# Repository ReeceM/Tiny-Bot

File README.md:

Tiny-Bot
========

ATTiny light influenced robot source code and board design files

This is the repository for the Tiny Bot that I designed after being influenced by the design of born 2 craft light bot.

Code
========
The code is written in the Arduino IDE as it was the quickest way to change and flash code when building(to me).
I plan to change it over to to correct C++ in months to come to shrink code size.

Design 
========

The design can be found at http://bariumelectronics.blogspot.com/2014/12/tiny-bot.html

Please feel free to edit and share your ideas :)

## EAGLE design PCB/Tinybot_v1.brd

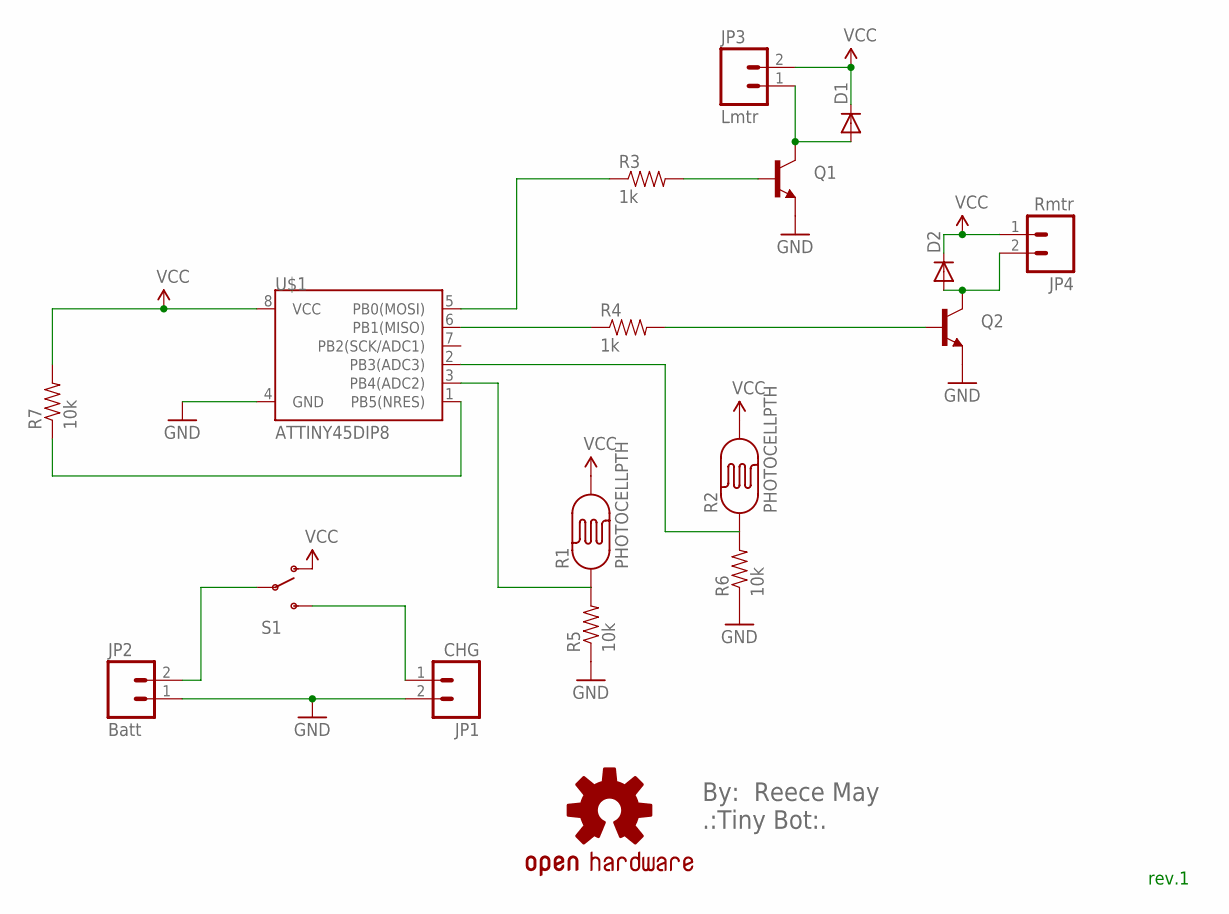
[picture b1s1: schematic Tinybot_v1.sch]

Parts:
D1, D2: DIODESOD; SOD-323
JP1: CHG; 1X02
JP2: Batt; 1X02
JP3: Lmtr; 1X02
JP4: Rmtr; 1X02
Q1, Q2: TRANSISTOR_NPNSOT23; SOT23
R1, R2: PHOTOCELLPTH; PHOTOCELL
R3, R4: 1k; 0805
R5, R6, R7: 10k; 0805
S1: SWITCH-SPST-SMD-A
U$1: ATTINY45DIP8; DIP08
U$2: OSHW-LOGOM; OSHW-LOGO-M

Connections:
GND: JP1.2, JP2.1, Q1.2 (E), Q2.2 (E), R5.1, R6.1, U$1.4 (GND)
unnamed: R3.1, U$1.5 (PB0(MOSI))
unnamed: R4.1, U$1.6 (PB1(MISO))
unnamed: Q1.1 (B), R3.2
unnamed: Q2.1 (B), R4.2
unnamed: D1.2 (A), JP3.1, Q1.3 (C)
unnamed: D2.2 (A), JP4.2, Q2.3 (C)
unnamed: JP2.2, S1.2
unnamed: JP1.1, S1.3 (S)
unnamed: R2.1, R6.2, U$1.2 (PB3(ADC3))
unnamed: R1.1, R5.2, U$1.3 (PB4(ADC2))
unnamed: R7.1, U$1.1 (PB5(NRES))
VCC: D1.1 (C), D2.1 (C), JP3.2, JP4.1, R1.2, R2.2, R7.2, S1.1 (O), U$1.8 (VCC)

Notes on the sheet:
By: Reece May .:Tiny Bot:.
rev.1

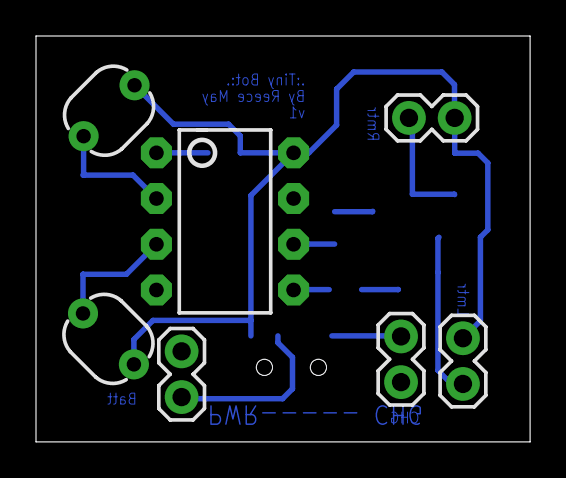
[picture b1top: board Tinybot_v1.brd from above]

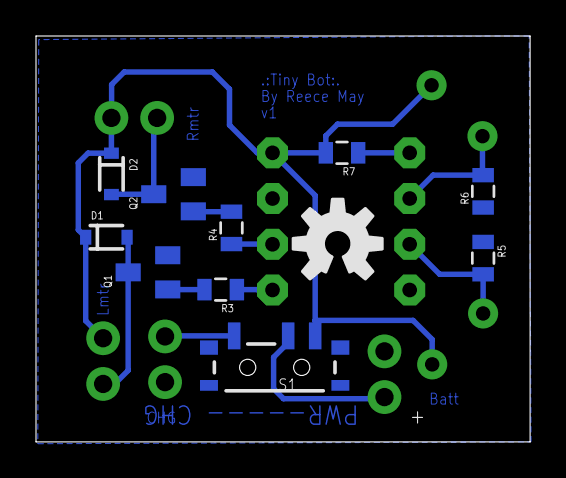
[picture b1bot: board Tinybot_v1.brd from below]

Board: 2 copper layers, 27.4 x 22.6 mm, 18 parts (11 on the bottom side), 13 nets.

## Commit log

2015-06-24 changed blog URL

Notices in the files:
parts and their libraries:
SparkFun: Licensing: CC v3.0 Share-Alike You are welcome to use this library for commercial purposes.
